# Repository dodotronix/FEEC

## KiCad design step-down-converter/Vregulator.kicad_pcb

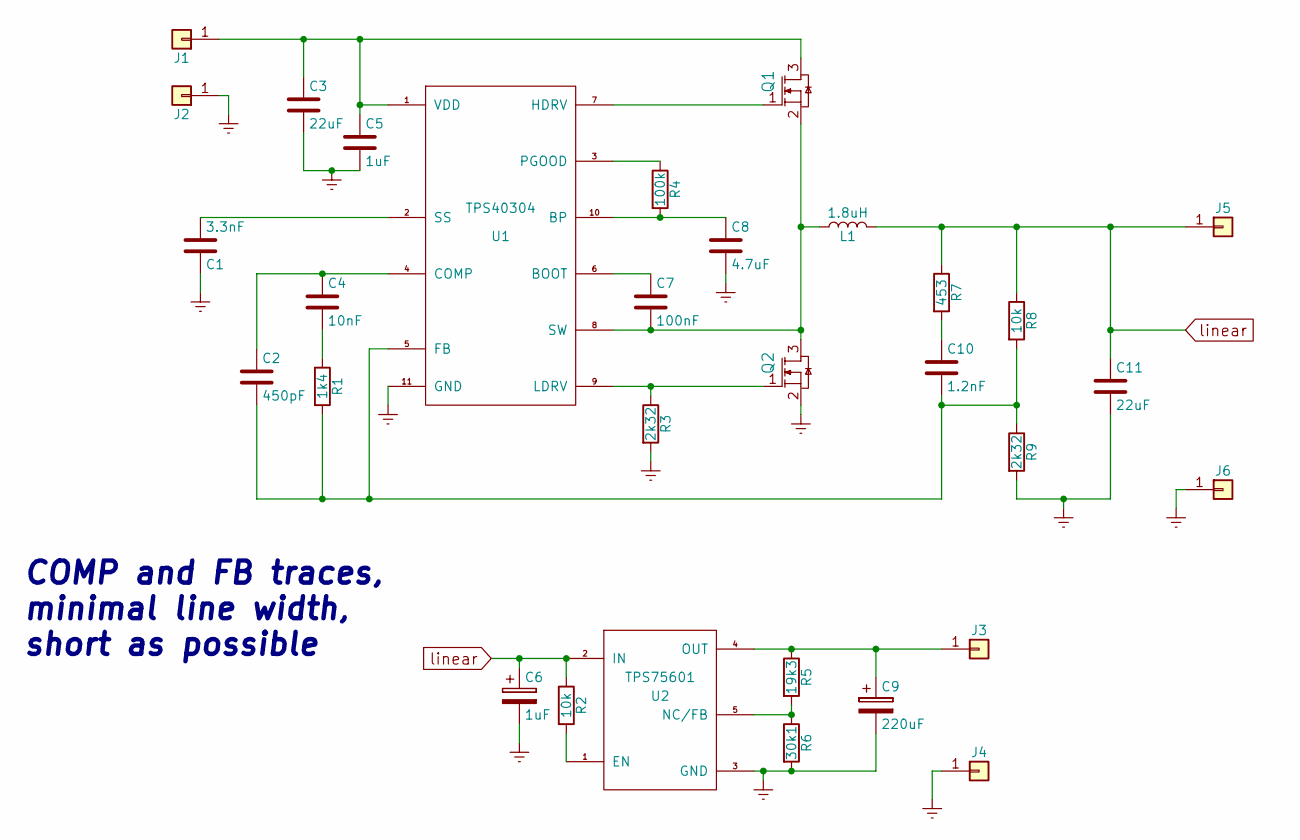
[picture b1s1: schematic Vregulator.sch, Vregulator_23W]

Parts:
C1: 3.3nF; R_1206
C2: 450pF; R_1206
C3, C11: 22uF; R_1206
C4: 10nF; R_1206
C5: 1uF; R_1206
C6: 1uF; C_1206
C7: 100nF; R_0805
C8: 4.7uF; R_0805
C9: 220uF; CP_Elec_6.3x7.7
C10: 1.2nF; R_1206
J1, J2, J3, J4, J5, J6: Conn_01x01; Test_Point_Keystone_5015_Micro-Minature
L1: 1.8uH; L_Vishay_IHLP-4040
Q1, Q2: IGFET_N; VSON-8_3.3x3.3mm_Pitch0.65mm_NexFET
R1: 1k4; R_1206
R2, R8: 10k; R_1206
R3, R9: 2k32; R_1206
R4: 100k; R_1206
R5: 19k3; R_0805
R6: 30k1; R_0805
R7: 453; R_1206
U1: TPS40304; VSON-10-1EP_3x3mm_Pitch0.5mm_ThermalPad
U2: TPS75601; TO-263-5_TabPin3

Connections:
GNDREF: C1.1, C3.2, C5.2, C6.2, C8.2, C9.2, C11.2, J2.1, J4.1, J6.1, Q2.2, R3.2, R6.2, R9.2, U1.11 (GND), U2.3 (GND)
unnamed: C1.2, U1.2 (SS)
unnamed: C2.1, C4.1, U1.4 (COMP)
unnamed: C3.1, C5.1, J1.1, Q1.3, U1.1 (VDD)
unnamed: C4.2, R1.1
unnamed: C7.1, U1.6 (BOOT)
unnamed: C7.2, L1.1, Q1.2, Q2.3, U1.8 (SW)
unnamed: C8.1, R4.2, U1.10 (BP)
unnamed: C9.1, J3.1, R5.1, U2.4 (OUT)
unnamed: C10.1, R7.2
unnamed: C2.2, C10.2, R1.2, R8.2, R9.1, U1.5 (FB)
unnamed: Q1.1, U1.7 (HDRV)
unnamed: Q2.1, R3.1, U1.9 (LDRV)
unnamed: R2.2, U2.1 (EN)
unnamed: R4.1, U1.3 (PGOOD)
unnamed: R5.2, R6.1, U2.5 (NC/FB)
linear: C6.1, C11.1, J5.1, L1.2, R2.1, R7.1, R8.1, U2.2 (IN)

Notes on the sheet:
COMP and FB traces, minimal line width, short as possible

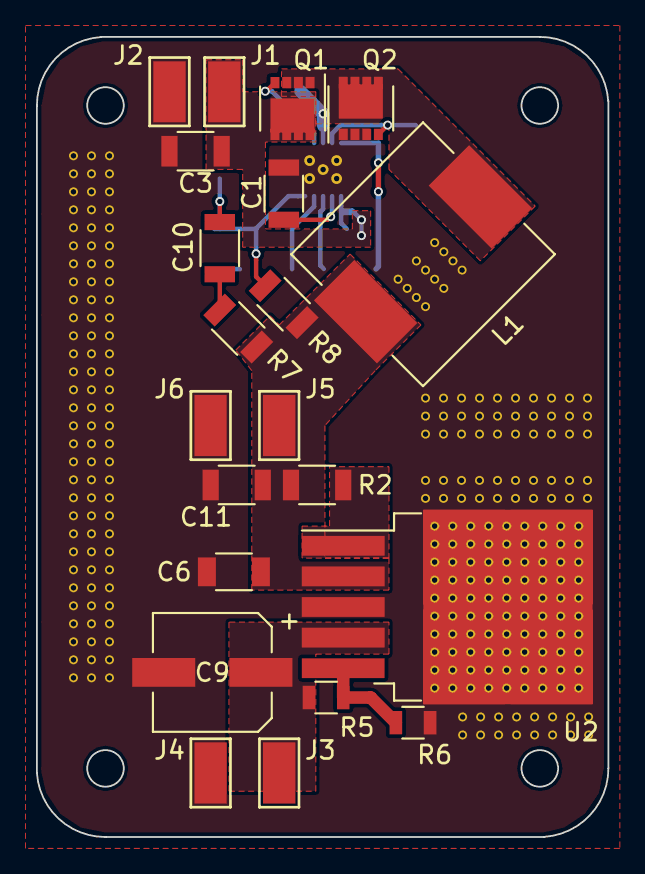
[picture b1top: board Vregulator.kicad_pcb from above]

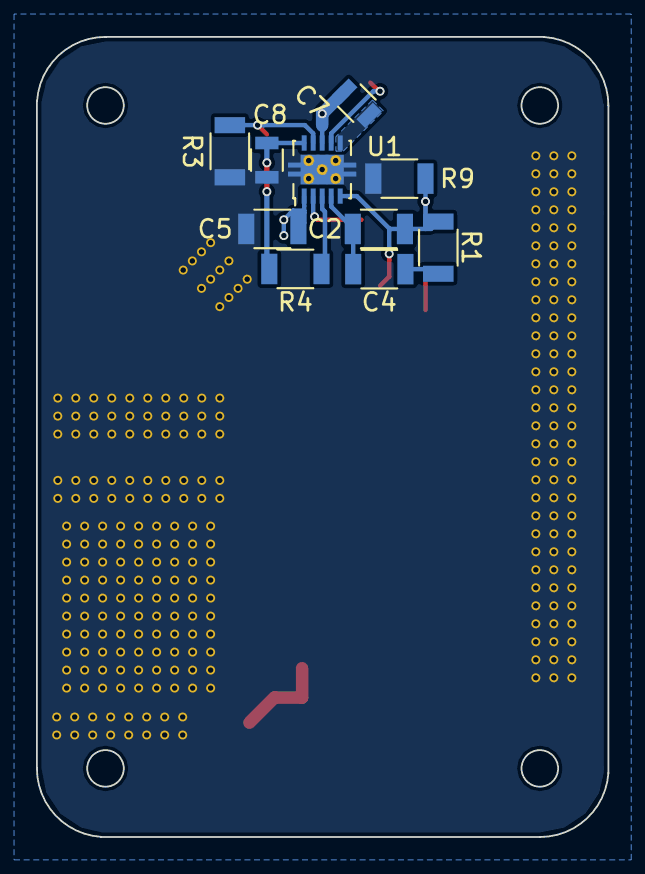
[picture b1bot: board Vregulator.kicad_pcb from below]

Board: 2 copper layers, 31.8 x 44.5 mm, 31 parts (10 on the bottom side), 17 nets.

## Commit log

2018-04-29 created new VHDL project
2018-04-29 CoolRunner board implementation constraints file
2018-04-29 UART module created
2018-04-29 fixed wrong indents
2018-05-02 project latex presentation
2018-05-19 changed location
2018-05-19 added kicad project
